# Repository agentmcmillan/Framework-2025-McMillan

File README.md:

# Framework-2025-Badge
Frame:Work NYC 2025 Interactive Pixel Badge Kitty - Badges Generously "sponsored" by Fuse Technical Group https://www.fuse-tg.com

# Getting started with the software.

## Tutorial Resources

Tutorial code for setting up the LED matrix display can be found here:
https://github.com/mkohler99/FrameworkNYBadge_Tutorials/

## Firmware Examples in This Repository

This repository includes several ready-to-use firmware examples:

### 1. LED Ripple Animation

Button-triggered rainbow ripple animation that demonstrates:
- LED matrix addressing and control
- Button input handling
- Safe power management (15% brightness limit)
- HSV to RGB color conversion
- Idle breathing animation

Press the center "MEOW" button to trigger a rainbow ripple effect emanating from the center of the display.

**Available in two versions:**
- **Arduino (Recommended)**: `LED_Ripple_Arduino/LED_Ripple_Arduino.ino` - Runs continuously with idle animation
- **MicroPython**: `led_ripple.py` - Simple script version

### 2. Badge LED + TFT Demo (Arduino)
**Directory:** `Badge_LED_TFT_Demo/`

Combines LED matrix control with a GC9A01 round TFT display (240×240) for enhanced interactivity:
- Rainbow ripple animation on LED matrix (center button triggered)
- Real-time battery voltage monitoring with color-coded display
- Button state indicators
- Simultaneous multi-display control
- Safe power management

**Required Hardware:**
- GC9A01 round TFT display connected via Whisker expansion port

**Documentation:**
- `README.md` - Complete feature overview
- `QUICK_START.md` - 5-minute setup guide
- `WIRING.txt` - Pin connection details

### 3. Dual-MCU WiFi Integration (Arduino)
**Directory:** `Dual_MCU_Integration/`

Advanced system that adds WiFi and Bluetooth capabilities using an ESP32-S3 coprocessor connected via the SAO port:

**Features:**
- **WiFi Access Point** - Connect your phone to "PixelKitty-XXXX" network
- **Web-based LED Designer** - Draw custom patterns on a 15×7 grid in your browser
- **QR Code Display** - Shows WiFi credentials on TFT display (press RIGHT button)
- **Animated Cat** - Pixel art cat walks across TFT after QR timeout
- **BLE Beacon** - Broadcast custom messages via Bluetooth
- **I2C Communication** - RP2040 and ESP32-S3 communicate at 100kHz

**Firmware Versions:**
- **Basic:** `RP2040_Master/` + `ESP32_S3_Slave/` - I2C foundation
- **Enhanced:** `RP2040_Enhanced/` + `ESP32_S3_Enhanced/` - Full features (QR, cat, web)

**Web Interface:**
- `Web_Interface/led_matrix.html` - Interactive LED pattern designer

**Required Hardware:**
- ESP32-S3 development board connected to SAO port (4-pin I2C)

**Comprehensive Documentation:**
- `README.md` - System architecture overview
- `GETTING_STARTED.md` - Quick start guide
- `ENHANCED_FEATURES.md` - QR code and web interface details
- `LIBRARY_SETUP.md` - Required Arduino libraries
- `ESP32_S3_SETUP.md` - Board support installation
- `WIRING.txt` - SAO port connection diagram
- `INDEX.md` - File organization guide
- `FUTURE_FEATURES.md` - Planned expansions

## Graphics Libraries

### Seeed_GFX Library
**Directory:** `Seeed_GFX-master/`

TFT_eSPI-based graphics library with 188+ example sketches for TFT displays:
- Clock displays, animations, sprites
- Touch panel support
- PNG/JPG decoding
- GUI widgets (buttons, meters, sliders)
- E-Paper display support
- DMA acceleration for RP2040

### Seeed Round Display Library
**Directory:** `Seeed_Arduino_RoundDisplay-main/`

LVGL-based UI library for round TFT displays with hardware test sketches and GIF player support.

## Repository Structure

```
Framework-2025-McMillan/
├── HARDWARE/                          # Hardware design files
│   ├── KiCad/TagTag/                 # KiCad project (schematic, PCB, libraries)
│   ├── Gerber/                       # Manufacturing files (ready for PCB fab)
│   └── Documentation/                # PDFs, BOM, 3D models, renders
├── LED_Ripple_Arduino/               # Arduino: Rainbow ripple animation (recommended)
├── Badge_LED_TFT_Demo/               # Arduino: LED matrix + TFT display demo
├── Dual_MCU_Integration/             # Arduino: ESP32-S3 WiFi/BLE expansion
│   ├── RP2040_Master/                # Basic I2C master firmware
│   ├── RP2040_Enhanced/              # Enhanced with QR code + animated cat
│   ├── ESP32_S3_Slave/               # Basic I2C slave with WiFi/BLE
│   ├── ESP32_S3_Enhanced/            # Enhanced with web server + captive portal
│   └── Web_Interface/                # Browser-based LED designer
├── Seeed_GFX-master/                 # TFT graphics library (188+ examples)
├── Seeed_Arduino_RoundDisplay-main/  # LVGL library for round displays
├── led_ripple.py                     # MicroPython LED animation example
└── README.md                         # This file
```

# Getting started with the hardware.

The FrameWork badge was designed with the following features

Easy to use RP2040 platform for hacking
Low Resolution 15x7 Pixel Matrix Display
4MB of on board flash storage
3 Buttons and a dedicated power switch
USB Type C for power and uploading software
2x AA battery holder for power on the go
Infrared Sender and Receiver for interactive experiences
Optional expansion headers for hardware hacking

Getting started with the RP2040
The raspberry pi RP2040 chip is super easy to use. Because this design is based on the Raspberry Pi Pico, a wide variety of tutorials and example code exists for this platform. 

More information about the RP2040 can be found here https://www.raspberrypi.com/documentation/microcontrollers/silicon.html#rp2040

This guide from Adafruit is super helpful for understand how to setup an Arduino style development environment
https://learn.adafruit.com/adafruit-feather-rp2040-pico/arduino-ide-setup

To program the Badge, simply put it in bootloader mode by plugging it into the computer you want to program it with, holding down the 'BOOT' button and then tapping the 'RESET' button. This will cause the RP2040 to start in bootloader mode and enumerate as a USB drive on the host computer. Compiled code can be copied to the device in this state and will run on reboot. Alternatively, various development environments can flash the chip while it's in this state. We recommend starting with Arduino, or if you are more comfortable with C/C++, Visual Studio Code.

# Getting Started With Framework Badge and Arduino

<<ARDUINO EXAMPLE>>

# Framework Badge Pinout

The RP2040 references its pins with an IO number. Your code will use these numbers to refer to the devices you wish to control. For example, if you want to blink the onboard status LED (labelled "Blink!") you would define and output pin on IO#11, as that LED is wired to IO#11.

Your badge has the following IO available:

## LED Matrix Display - IO#4

The LED Matrix is an array of WS2812B-2020 RGB LEDs arranged in a 15 column by 7 row grid. The LED's are addressed from Top Left to Bottom Right in columns going from top to bottom. The first Column is made of LEDs 1-7, the next 8-14, the next 15-21, and so on. The connection of the LEDs **DOES NOT** flow snake-wise, columns are always numbered from top to bottom. 

When using a large number of these LEDs power draw can get out of control. Each LED channel 'Red' 'Green' or 'Blue' can use up to 12mA of current, for a total of 36mA per LED. With 107 LED's you could theoretically draw up to 3,852mA of current, however the board can really only supply around 2500mA of current reliably. For this reason, 

**NEVER POWER THE LED MATRIX AT FULL BRIGHTNESS IN WHITE**

. Many LED software libraries, such as FastLED have the ability to estimate power usage at runtime to set proper maximum levels that vary dynamically with the number of pixels lit and what color they are. In our normal Badge Application, drawing text on the display, we statistically light up less than 1/4 of the pixels at any given moment, and have the brightness set to less than 25%. This gives us at least 8 hours of run time on batteries and keeps the power usage within reasonable limits, plus the LED's are distractingly too bright at full power anyway. **Failure to properly manage the LED matrix's power can result in hardware damage, quickly depleted batteries, and risk of burns from overheated components, so please be careful**

More information about he WS2812B 2020 LEDs used in this project can be found at the data sheet here: 
https://www.lcsc.com/datasheet/C965555.pdf

## Infrared Transmitter - IO#3

The Infrared TX is simply an Infrared LED that you can blink on and off really fast to send data, like a universal remote. (In fact, if you wanted to you could probably program your badge to emulate remote control signals and wreak havoc in a Buffalo Wild Wings, but please use this feature responsibly) This LED emits light in the 940nm range, typical for IR applications. In our laser tag application we're using a 38khz modulation scheme, which is common for remote control applications.

## Buttons - IO#5, 6, and 7

IO Pins can also be configured as inputs to read the state of buttons. The buttons on this badge are normally open and are considered pressed when they are pulled to ground. The buttons are IO#5-7 from Left to Right

## Infrared Receiver - IO#27

The Infrared Receiver used is specifically designed for Remote Control applications and is designed specifically for 38khz modulated signals. This means that there is logic in the receiver itself designed to filter out noise at other frequencies, such as fluorescent lighting. 

More information about the IRM-H638T/TR2 can be found at the data sheet here:
https://www.everlighteurope.com/custom/files/datasheets/DMO-0000008.pdf

## Battery Voltage Monitor - IO#26

The badge has the ability to monitor the voltage of the AA batteries through a voltage divider. The voltage divider scales the voltage by .357 allowing for you to measure the battery voltage in a range of 0-9v (However it should never exceed 3v. 

## Red LED - IO#11

The badge features a simple LED you can blink on and off for testing

## USB Port

The onboard USB port can be configured with various libraries, such as Tiny USB, for all sorts of neat applications, from serial interfaces to keyboard emulators, to audio devices. We've used this chip's USB functionality in the past to emulate a USB sound card to provide timecode to windows computers.

# Expansion Port Pinouts

## Expansion "Whisker" Port

Because our badge is kitty cat shaped, we named our expansion ports 'Whiskers' Many dev boards create their own custom standards for expansion boards, so why cant us.

These ports are usually non soldered on production badges, however simple 1x5 header sockets can be soldered in place to allow for modules to stack onto the bottom side of the board. 

The following IO is available:
- **+5V** - For powering LEDs
- **+3.3V** - For powering other devices
- **GND** - Very important
- **IO#23, 24, and 25** - For connecting to various external devices (SPI/I2C capable)
- **IO#28 (ADC#2)** - A special analog input pin that can read voltages, useful for sensors

### TFT Display Expansion

The Whisker port is ideal for connecting TFT displays via SPI. This repository includes two graphics libraries (`Seeed_GFX-master/` and `Seeed_Arduino_RoundDisplay-main/`) with 188+ example sketches for driving TFT displays.

**Common TFT Pin Mapping (via Whisker Port):**
- **SPI MOSI:** IO#23 or IO#24
- **SPI SCK:** IO#24 or IO#25
- **CS (Chip Select):** Any available GPIO
- **DC (Data/Command):** Any available GPIO
- **RST (Reset):** Any available GPIO (or tie to 3.3V rail)
- **Power:** 3.3V for logic, 5V for backlight (if needed)

See the `Badge_LED_TFT_Demo/` example for a complete implementation using a GC9A01 round display.

The following image shows how these pins are laid out. The schematic and PCB files included in this repository can show how to build a board that connects to this expansion port.

## DVI "Whisker" Port

We chose to add DVI output to our board using an existing open source board called the DVI Sock. This board connects a specific set of IO pins to an HDMI plug in order to allow the RP2040 to drive a display with a 640x480 DVI signal. 

The DVI Sock can be found here:
https://www.adafruit.com/product/5957

More information about the DVI Sock and its implementation can be found at the original creator's GitHub: 
https://github.com/Wren6991/Pico-DVI-Sock
We take no credit for how this feature works, we are simply passing the needed IO through our board from the RP2040 to the pins for the expansion board to make it easier to experiment with this functionality. 

The DVI expansion uses IO#12-IO#19

## SAO Port

In the badge hacking community, a standard developed for connecting Simple Add Ons to existing hardware badges, using a 4-6 pin socket on the badge with matching pins on the add on. This allows for hackers to dress their badges up with flair that pulls power from the main badge. We are able to re-use some of the whisker header pins in a slightly different shape to allow for a basic 4 pin SAO port, when a header is soldered to the top side of the badge. 

More information about the SAO standard can be found on the creator's page here:
https://hackaday.io/project/52950-shitty-add-ons/log/159806-introducing-the-shitty-add-on-v169bis-standard
We only implement the v0.1 version of this standard with 4 pins, however a full 6 pin SAO will fit mechanically without conflict

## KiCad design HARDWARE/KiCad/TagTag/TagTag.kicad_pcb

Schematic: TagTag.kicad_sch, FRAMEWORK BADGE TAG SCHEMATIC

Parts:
BT1, BT2: BH-AA-A5BJ012; BAT_BH-AA-A5BJ012; PARTREV D; LCSC C5290180
C1, C2, C5, C6, C7, C8, C10, C11, C13, C16: 100nF; C_0603_1608Metric; LCSC C5137636
C3, C4, C20, C27, C28: 1uF; C_0603_1608Metric; LCSC C5137472
C9, C12: 10uF; C_0603_1608Metric; LCSC C5137497
C14, C15: 22pF; C_0603_1608Metric; LCSC C7419421
C23, C30: 10uF; C_0805_2012Metric; LCSC C1713
C24, C25, C26: 47uF; C_0805_2012Metric; LCSC C16780
C29: 22uF; C_0805_2012Metric; LCSC C5137600
D1, D2, D3: LED 0805 RED; LED_0805_2012Metric; LCSC C965812
D5: IR15-21C/TR8; LED_1206_3216Metric; LCSC C22357565
D301, D302, D303, D304, D305, D306, D307, D308, D309, D310, D311, D312, D313, D314, D315, D316, D317, D318, D319, D320, D321, D322, D323, D324, D325, D326, D327, D328, D329, D330, D331, D332, D333, D334, D335, D336, D337, D338, D339, D340, D341, D342, D343, D344, D345, D346, D347, D348, D349, D350, D351, D352, D353, D354, D355, D356, D357, D358, D359, D360, D361, D362, D363, D364, D365, D366, D367, D368, D369, D370, D371, D372, D373, D374, D375, D376, D377, D378, D379, D380, D381, D382, D383, D384, D385, D386, D387, D388, D389, D390, D391, D392, D393, D394, D395, D396, D397, D398, D399, D400, D401, D402, D403, D404, D405: WS2812B-2020; LED_WS2812B-2020_PLCC4_2.0x2.0mm; LCSC C965555
EAR1, EAR2: Fiducial; Fiducial_1mm_Mask2mm; Manufacturer_Part_Number DNP; LCSC DNP
FID3: Fiducial; Fiducial_1mm_Mask2mm; Manufacturer_Part_Number DNP; LCSC DNP
H7, H8: MountingHole_Pad; MountingHole_2.7mm_M2.5_DIN965_Pad; LCSC DNP
IC1: IRM-H638T_TR2; IRMH638TTR2; Mouser Part Number 638-IRMH638TTR2
J1: GT-USB-7010ASV; USB_C_Receptacle_G-Switch_GT-USB-7010ASV; PARTREV A0; LCSC C2988369
J2: Conn_01x02_Pin; PinHeader_1x02_P2.54mm_Vertical; LCSC DNP
L1: TMPA 0603S-1R0MN-D; LCSC C305186
Q1: AO3406; Manufacturer_Part_Number AO3406; LCSC C2909910
R1, R4: 27.4; R_0603_1608Metric; LCSC C185346
R2: 180K; R_0603_1608Metric; LCSC C123419
R3: 100K; R_0603_1608Metric; LCSC C14675
R5, R6: 5.1K; R_0603_1608Metric; LCSC C105580
R7: 270; R_0603_1608Metric; LCSC C22966
R8: 750; R_0603_1608Metric; LCSC C23241
R10, R13, R16, R27: 10K; R_0603_1608Metric; LCSC C98220
R17: 732K; R_0603_1608Metric; LCSC C246003
R18: 91K; R_0603_1608Metric; LCSC C137671
R21: 120; R_0603_1608Metric; LCSC C177328
R26, R28: 1K; R_0603_1608Metric; LCSC C22548
R29: 150; R_0603_1608Metric; LCSC C114608
SW1, SW3, SW4: GT-TC149A-H060-L1; GT-TC149X; LCSC C2834980
SW2, SW5: PTS526SK08SMTR2LFS; PTS526_0P8_CNK; LCSC C2800848
SW8: MK-12C02-G025; MK-12C02; LCSC C778186
TP1: TestPoint; TestPoint_Pad_1.0x1.0mm; LCSC DNP
U2: RP2040; QFN-56-1EP_7x7mm_P0.4mm_EP3.2x3.2mm; LCSC C2040
U3: SN74LV1T34; SOT-23-5; Manufacturer_Part_Number SN74LV1T34; LCSC C100024
U4: TPS61022RWUR; CONV_TPS61022RWUR; PARTREV 4223724/C 02/2018; LCSC C915088
U5: LM66200DRLR; SOT-5X3_DRL_TEX; LCSC C3235556
U6: AMS1117-3.3; SOT229P700X180-4N; PARTREV NA; LCSC C347222
U7: W25Q32JVSSIQ; SOIC-8_5.23x5.23mm_P1.27mm; LCSC C179173
WIS1, WIS2, WIS3, WIS4: Conn_01x05_Pin; PinSocket_1x05_P2.54mm_Vertical; LCSC DNP
Y1: ABLS-12.000MHZ-B4-T; XTAL_ABLS-12.000MHZ-B4-T; PARTREV 02.16.2021; LCSC C596818

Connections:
+1V1: C1.1, C2.1, C3.1, U2.23 (DVDD), U2.45 (VREG_VOUT), U2.50 (DVDD)
+5V: C30.1, D301.4 (VDD), D302.4 (VDD), D303.4 (VDD), D304.4 (VDD), D305.4 (VDD), D306.4 (VDD), D307.4 (VDD), D308.4 (VDD), D309.4 (VDD), D310.4 (VDD), D311.4 (VDD), D312.4 (VDD), D313.4 (VDD), D314.4 (VDD), D315.4 (VDD), D316.4 (VDD), D317.4 (VDD), D318.4 (VDD), D319.4 (VDD), D320.4 (VDD), D321.4 (VDD), D322.4 (VDD), D323.4 (VDD), D324.4 (VDD), D325.4 (VDD), D326.4 (VDD), D327.4 (VDD), D328.4 (VDD), D329.4 (VDD), D330.4 (VDD), D331.4 (VDD), D332.4 (VDD), D333.4 (VDD), D334.4 (VDD), D335.4 (VDD), D336.4 (VDD), D337.4 (VDD), D338.4 (VDD), D339.4 (VDD), D340.4 (VDD), D341.4 (VDD), D342.4 (VDD), D343.4 (VDD), D344.4 (VDD), D345.4 (VDD), D346.4 (VDD), D347.4 (VDD), D348.4 (VDD), D349.4 (VDD), D350.4 (VDD), D351.4 (VDD), D352.4 (VDD), D353.4 (VDD), D354.4 (VDD), D355.4 (VDD), D356.4 (VDD), D357.4 (VDD), D358.4 (VDD), D359.4 (VDD), D360.4 (VDD), D361.4 (VDD), D362.4 (VDD), D363.4 (VDD), D364.4 (VDD), D365.4 (VDD), D366.4 (VDD), D367.4 (VDD), D368.4 (VDD), D369.4 (VDD), D370.4 (VDD), D371.4 (VDD), D372.4 (VDD), D373.4 (VDD), D374.4 (VDD), D375.4 (VDD), D376.4 (VDD), D377.4 (VDD), D378.4 (VDD), D379.4 (VDD), D380.4 (VDD), D381.4 (VDD), D382.4 (VDD), D383.4 (VDD), D384.4 (VDD), D385.4 (VDD), D386.4 (VDD), D387.4 (VDD), D388.4 (VDD), D389.4 (VDD), D390.4 (VDD), D391.4 (VDD), D392.4 (VDD), D393.4 (VDD), D394.4 (VDD), D395.4 (VDD), D396.4 (VDD), D397.4 (VDD), D398.4 (VDD), D399.4 (VDD), D400.4 (VDD), D401.4 (VDD), D402.4 (VDD), D403.4 (VDD), D404.4 (VDD), D405.4 (VDD), R16.1, R21.1, U3.5 (VCC), U5.2 (VOUT), U5.7 (VOUT), U6.3 (VIN), WIS3.5
+BATT: C23.1, L1.1, R2.1, SW8.3 (C), U4.5 (EN), U4.7 (VIN)
/5V_PXL: D301.3 (DIN), U3.4 (Y)
/AN_ADC2: U2.40 (GPIO28_ADC2), WIS4.1
/AN_BATT_MEASURE_PI: R2.2, R3.1, U2.38 (GPIO26_ADC0)
/DI_23: U2.35 (GPIO23), WIS4.5
/DI_24: J2.2, U2.36 (GPIO24), WIS4.4
/DI_25: U2.37 (GPIO25), WIS3.3, WIS4.2
/DI_BTN_FIRE_PI: SW4.1, SW4.2, U2.9 (GPIO7)
/DI_BTN_L_PI: SW1.1, SW1.2, U2.7 (GPIO5)
/DI_BTN_R_PI: SW3.1, SW3.2, U2.8 (GPIO6)
/DI_IRM_PI: IC1.3 (OUT), U2.39 (GPIO27_ADC1)
/DO_IR_LED_PI: Q1.1 (G), R10.1, U2.5 (GPIO3)
/DVI_12: U2.15 (GPIO12), WIS2.1
/DVI_13: U2.16 (GPIO13), WIS2.2
/DVI_14: U2.17 (GPIO14), WIS2.4
/DVI_15: U2.18 (GPIO15), WIS2.5
/DVI_16: U2.27 (GPIO16), WIS1.5
/DVI_17: U2.28 (GPIO17), WIS1.4
/DVI_18: U2.29 (GPIO18), WIS1.2
/DVI_19: U2.30 (GPIO19), WIS1.1
/GPIO_PXL_PI: U2.6 (GPIO4), U3.2 (A)
/PI_A_3v3: C4.1, C5.1, C6.1, C7.1, C8.1, C9.1, C10.1, C11.1, C13.1, C16.1, C20.1, C29.1, D2.2 (A), IC1.4 (VCC), R13.2, R27.2, U2.1 (IOVDD), U2.10 (IOVDD), U2.22 (IOVDD), U2.33 (IOVDD), U2.42 (IOVDD), U2.43 (ADC_AVDD), U2.44 (VREG_IN), U2.48 (USB_VDD), U2.49 (IOVDD), U6.2 (VOUT), U6.4 (VOUT_(TAB)), U7.8 (VCC), WIS3.1, WIS3.2
/PI_A_LED: D3.2 (A), U2.14 (GPIO11)
/PI_A_USB_C_Data_1_N: R4.2, U2.46 (USB_DM)
/PI_A_USB_C_Data_1_P: R1.2, U2.47 (USB_DP)
/PI_A_USB_C_Data_N: J1.A7 (D1-), J1.B7 (D2-), R4.1
/PI_A_USB_C_Data_P: J1.A6 (D1+), J1.B6 (D2+), R1.1
/PI_A_USB_PWR_IN: C12.1, C28.1, D1.2 (A), J1.A4_B9 (VBUS_A), J1.B4_A9 (VBUS_B), U5.6 (VIN2)
/PI_BOOT: R26.1, SW5.1, SW5.2, TP1.1
/PI_RESET: R13.1, SW2.1, SW2.2, U2.26 (RUN)
/QSPI_SCLK_A: U2.52 (QSPI_SCLK), U7.6 (CLK)
/QSPI_SD0_A: U2.53 (QSPI_SD0), U7.5 (DI(IO0))
/QSPI_SD1_A: U2.55 (QSPI_SD1), U7.2 (DO(IO1))
/QSPI_SD2_A: U2.54 (QSPI_SD2), U7.3 (IO2)
/QSPI_SD3_A: U2.51 (QSPI_SD3), U7.7 (IO3)
/QSPI_SS: R26.2, R27.1, U2.56 (QSPI_SS), U7.1 (~CS)
/XIN_A: C15.1, U2.20 (XIN), Y1.1
/XOUT_A: R28.2, U2.21 (XOUT)
GND: BT2.-, C1.2, C2.2, C3.2, C4.2, C5.2, C6.2, C7.2, C8.2, C9.2, C10.2, C11.2, C12.2, C13.2, C14.2, C15.2, C16.2, C20.2, C23.2, C24.2, C25.2, C26.2, C27.2, C28.2, C29.2, C30.2, D301.2 (VSS), D302.2 (VSS), D303.2 (VSS), D304.2 (VSS), D305.2 (VSS), D306.2 (VSS), D307.2 (VSS), D308.2 (VSS), D309.2 (VSS), D310.2 (VSS), D311.2 (VSS), D312.2 (VSS), D313.2 (VSS), D314.2 (VSS), D315.2 (VSS), D316.2 (VSS), D317.2 (VSS), D318.2 (VSS), D319.2 (VSS), D320.2 (VSS), D321.2 (VSS), D322.2 (VSS), D323.2 (VSS), D324.2 (VSS), D325.2 (VSS), D326.2 (VSS), D327.2 (VSS), D328.2 (VSS), D329.2 (VSS), D330.2 (VSS), D331.2 (VSS), D332.2 (VSS), D333.2 (VSS), D334.2 (VSS), D335.2 (VSS), D336.2 (VSS), D337.2 (VSS), D338.2 (VSS), D339.2 (VSS), D340.2 (VSS), D341.2 (VSS), D342.2 (VSS), D343.2 (VSS), D344.2 (VSS), D345.2 (VSS), D346.2 (VSS), D347.2 (VSS), D348.2 (VSS), D349.2 (VSS), D350.2 (VSS), D351.2 (VSS), D352.2 (VSS), D353.2 (VSS), D354.2 (VSS), D355.2 (VSS), D356.2 (VSS), D357.2 (VSS), D358.2 (VSS), D359.2 (VSS), D360.2 (VSS), D361.2 (VSS), D362.2 (VSS), D363.2 (VSS), D364.2 (VSS), D365.2 (VSS), D366.2 (VSS), D367.2 (VSS), D368.2 (VSS), D369.2 (VSS), D370.2 (VSS), D371.2 (VSS), D372.2 (VSS), D373.2 (VSS), D374.2 (VSS), D375.2 (VSS), D376.2 (VSS), D377.2 (VSS), D378.2 (VSS), D379.2 (VSS), D380.2 (VSS), D381.2 (VSS), D382.2 (VSS), D383.2 (VSS), D384.2 (VSS), D385.2 (VSS), D386.2 (VSS), D387.2 (VSS), D388.2 (VSS), D389.2 (VSS), D390.2 (VSS), D391.2 (VSS), D392.2 (VSS), D393.2 (VSS), D394.2 (VSS), D395.2 (VSS), D396.2 (VSS), D397.2 (VSS), D398.2 (VSS), D399.2 (VSS), D400.2 (VSS), D401.2 (VSS), D402.2 (VSS), D403.2 (VSS), D404.2 (VSS), D405.2 (VSS), H7.1, H8.1, IC1.1 (GND_1), IC1.2 (GND_2), J1.A1_B12 (GND_A), J1.B1_A12 (GND_B), J1.SH1 (SHIELD), J1.SH2 (SHIELD), J1.SH3 (SHIELD), J1.SH4 (SHIELD), J2.1, Q1.2 (S), R3.2, R5.2, R6.2, R7.1, R8.1, R10.2, R18.2, R29.1, SW1.3, SW1.4, SW2.3, SW2.4, SW3.3, SW3.4, SW4.3, SW4.4, SW5.3, SW5.4, U2.19 (TESTEN), U2.57 (GND), U3.3 (GND), U4.1 (GND), U4.6 (MODE), U5.1 (GND), U5.4 (ON), U5.5 (GND), U6.1 (ADJ/GND), U7.4 (GND), WIS1.3, WIS2.3, WIS4.3
unnamed: BT1.-, BT2.+
unnamed: C14.1, R28.1, Y1.2
unnamed: D1.1 (K), R7.2
unnamed: D2.1 (K), R8.2
unnamed: D3.1 (K), R29.2
unnamed: D5.2 (A), R21.2
unnamed: D5.1 (K), Q1.3 (D)
unnamed: D301.1 (DOUT), D302.3 (DIN)
unnamed: D302.1 (DOUT), D303.3 (DIN)
unnamed: D303.1 (DOUT), D304.3 (DIN)
unnamed: D304.1 (DOUT), D305.3 (DIN)
unnamed: D305.1 (DOUT), D306.3 (DIN)
unnamed: D306.1 (DOUT), D307.3 (DIN)
unnamed: D307.1 (DOUT), D308.3 (DIN)
unnamed: D308.1 (DOUT), D309.3 (DIN)
unnamed: D309.1 (DOUT), D310.3 (DIN)
unnamed: D310.1 (DOUT), D311.3 (DIN)
unnamed: D311.1 (DOUT), D312.3 (DIN)
unnamed: D312.1 (DOUT), D313.3 (DIN)
unnamed: D313.1 (DOUT), D314.3 (DIN)
unnamed: D314.1 (DOUT), D315.3 (DIN)
unnamed: D315.1 (DOUT), D316.3 (DIN)
unnamed: D316.1 (DOUT), D317.3 (DIN)
unnamed: D317.1 (DOUT), D318.3 (DIN)
unnamed: D318.1 (DOUT), D319.3 (DIN)
unnamed: D319.1 (DOUT), D320.3 (DIN)
unnamed: D320.1 (DOUT), D321.3 (DIN)
unnamed: D321.1 (DOUT), D322.3 (DIN)
unnamed: D322.1 (DOUT), D323.3 (DIN)
unnamed: D323.1 (DOUT), D324.3 (DIN)
unnamed: D324.1 (DOUT), D325.3 (DIN)
unnamed: D325.1 (DOUT), D326.3 (DIN)
unnamed: D326.1 (DOUT), D327.3 (DIN)
unnamed: D327.1 (DOUT), D328.3 (DIN)
unnamed: D328.1 (DOUT), D329.3 (DIN)
unnamed: D329.1 (DOUT), D330.3 (DIN)
unnamed: D330.1 (DOUT), D331.3 (DIN)
unnamed: D331.1 (DOUT), D332.3 (DIN)
unnamed: D332.1 (DOUT), D333.3 (DIN)
unnamed: D333.1 (DOUT), D334.3 (DIN)
unnamed: D334.1 (DOUT), D335.3 (DIN)
unnamed: D335.1 (DOUT), D336.3 (DIN)
unnamed: D336.1 (DOUT), D337.3 (DIN)
unnamed: D337.1 (DOUT), D338.3 (DIN)
unnamed: D338.1 (DOUT), D339.3 (DIN)
unnamed: D339.1 (DOUT), D340.3 (DIN)
unnamed: D340.1 (DOUT), D341.3 (DIN)
unnamed: D341.1 (DOUT), D342.3 (DIN)
unnamed: D342.1 (DOUT), D343.3 (DIN)
unnamed: D343.1 (DOUT), D344.3 (DIN)
unnamed: D344.1 (DOUT), D345.3 (DIN)
unnamed: D345.1 (DOUT), D346.3 (DIN)
unnamed: D346.1 (DOUT), D347.3 (DIN)
unnamed: D347.1 (DOUT), D348.3 (DIN)
unnamed: D348.1 (DOUT), D349.3 (DIN)
unnamed: D349.1 (DOUT), D350.3 (DIN)
unnamed: D350.1 (DOUT), D351.3 (DIN)
unnamed: D351.1 (DOUT), D352.3 (DIN)
unnamed: D352.1 (DOUT), D353.3 (DIN)
unnamed: D353.1 (DOUT), D354.3 (DIN)
unnamed: D354.1 (DOUT), D355.3 (DIN)
unnamed: D355.1 (DOUT), D356.3 (DIN)
unnamed: D356.1 (DOUT), D357.3 (DIN)
unnamed: D357.1 (DOUT), D358.3 (DIN)
unnamed: D358.1 (DOUT), D359.3 (DIN)
unnamed: D359.1 (DOUT), D360.3 (DIN)
unnamed: D360.1 (DOUT), D361.3 (DIN)
unnamed: D361.1 (DOUT), D362.3 (DIN)
unnamed: D362.1 (DOUT), D363.3 (DIN)
unnamed: D363.1 (DOUT), D364.3 (DIN)
unnamed: D364.1 (DOUT), D365.3 (DIN)
unnamed: D365.1 (DOUT), D366.3 (DIN)
unnamed: D366.1 (DOUT), D367.3 (DIN)
unnamed: D367.1 (DOUT), D368.3 (DIN)
unnamed: D368.1 (DOUT), D369.3 (DIN)
unnamed: D369.1 (DOUT), D370.3 (DIN)
unnamed: D370.1 (DOUT), D371.3 (DIN)
unnamed: D371.1 (DOUT), D372.3 (DIN)
unnamed: D372.1 (DOUT), D373.3 (DIN)
unnamed: D373.1 (DOUT), D374.3 (DIN)
unnamed: D374.1 (DOUT), D375.3 (DIN)
unnamed: D375.1 (DOUT), D376.3 (DIN)
unnamed: D376.1 (DOUT), D377.3 (DIN)
unnamed: D377.1 (DOUT), D378.3 (DIN)
unnamed: D378.1 (DOUT), D379.3 (DIN)
unnamed: D379.1 (DOUT), D380.3 (DIN)
unnamed: D380.1 (DOUT), D381.3 (DIN)
unnamed: D381.1 (DOUT), D382.3 (DIN)
unnamed: D382.1 (DOUT), D383.3 (DIN)
unnamed: D383.1 (DOUT), D384.3 (DIN)
unnamed: D384.1 (DOUT), D385.3 (DIN)
unnamed: D385.1 (DOUT), D386.3 (DIN)
unnamed: D386.1 (DOUT), D387.3 (DIN)
unnamed: D387.1 (DOUT), D388.3 (DIN)
unnamed: D388.1 (DOUT), D389.3 (DIN)
unnamed: D389.1 (DOUT), D390.3 (DIN)
unnamed: D390.1 (DOUT), D391.3 (DIN)
unnamed: D391.1 (DOUT), D392.3 (DIN)
unnamed: D392.1 (DOUT), D393.3 (DIN)
unnamed: D393.1 (DOUT), D394.3 (DIN)
unnamed: D394.1 (DOUT), D395.3 (DIN)
unnamed: D395.1 (DOUT), D396.3 (DIN)
unnamed: D396.1 (DOUT), D397.3 (DIN)
unnamed: D397.1 (DOUT), D398.3 (DIN)
unnamed: D398.1 (DOUT), D399.3 (DIN)
unnamed: D399.1 (DOUT), D400.3 (DIN)
unnamed: D400.1 (DOUT), D401.3 (DIN)
unnamed: D401.1 (DOUT), D402.3 (DIN)
unnamed: D402.1 (DOUT), D403.3 (DIN)
unnamed: D403.1 (DOUT), D404.3 (DIN)
unnamed: D404.1 (DOUT), D405.3 (DIN)
unnamed: J1.A5 (CC1), R5.1
unnamed: J1.B5 (CC2), R6.1
unnamed: BT1.+, SW8.2 (B)
unnamed: R17.2, R18.1, U4.4 (FB)
unnamed: L1.2, U4.2 (SW)
unnamed: C24.1, C25.1, C26.1, C27.1, R17.1, U4.3 (VOUT), U5.3 (VIN1)
unnamed: R16.2, U5.8 (ST)

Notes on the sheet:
RIGHT BUTTON IO#6
RP2040 MCU BASED ON RASPBERRY PI RP2040 MINIMAL DESIGN EXAMPLE https://datasheets.raspberrypi.com/rp2040/Minimal-KiCAD.zip
LED PIXEL ARRAY IO#4 - 15 Columns of 7
940NM LED 31mA
C513 by pin 44
EXPANSION HEADERS
BUTTONS
BOOT BUTTON
IDEAL DIODE SWITCHOVER - SELECT USB OR BATTERY POWER
PDN
LEVEL SHIFT FOR PIXEL DATA
INFRARED TRANSMITTER IO#3
RESET BUTTON
POWER SUPPLY
INFRARED RECEIVER - 38KHZ MODULATION BASED ON IRM-H638T/TR2 APPLICATION CIRCUIT IO#27
"MEOW" BUTTON IO#7
SAO BODGE ALLOWS SAO ADDONS TO MATE WITH WHISKER HEADER PIN 2 AND 3 (See Figure 1)
USB TYPE C CONNECTOR
Based on AMS1117 Typical Application Circuit 5V Input, 1 Amp @ 3.3V Output
RED LED IO#11
WIS3 PIN 3 IO#25
4MB SPI Flash
LEFT BUTTON IO#5
FIGURE 1, SAO PORT LAYOUT (PINOUT VIEWED FROM TOP)
BATTERY VOLTAGE SENSOR IO#26
INFRARED TRANSCIEVER
RP2040 - MAIN CPU
3.3V POWER SUPPLY - POWER FOR MCU AND LOGIC
Based on Texas Instruments WEBENCH design 2-3V Input, 2.5 Amp @ 5V Output, Efficiency: 88%
MECHANICAL / FABRICATION
J2 PIN 1 GND
Crystal
CC Resistors configured for 3A @ 5V
Based on Texas Instruments LM66200DLR Reference Design 5V Input, 2.5 Amp @ 5V Output
J2 PIN 2 IO#24
BATTERY SUPPLY AND POWER SWITCH
POWER STATUS LEDS
EXPANSION WHISKER MATES WITH CUSTOM EXPANSION WHISKER BOARDS
SPARKLING DVI HEADER MATES WITH ADAFRUIT DVI SOCK PART 5957 https://www.adafruit.com/product/5957
2.5A

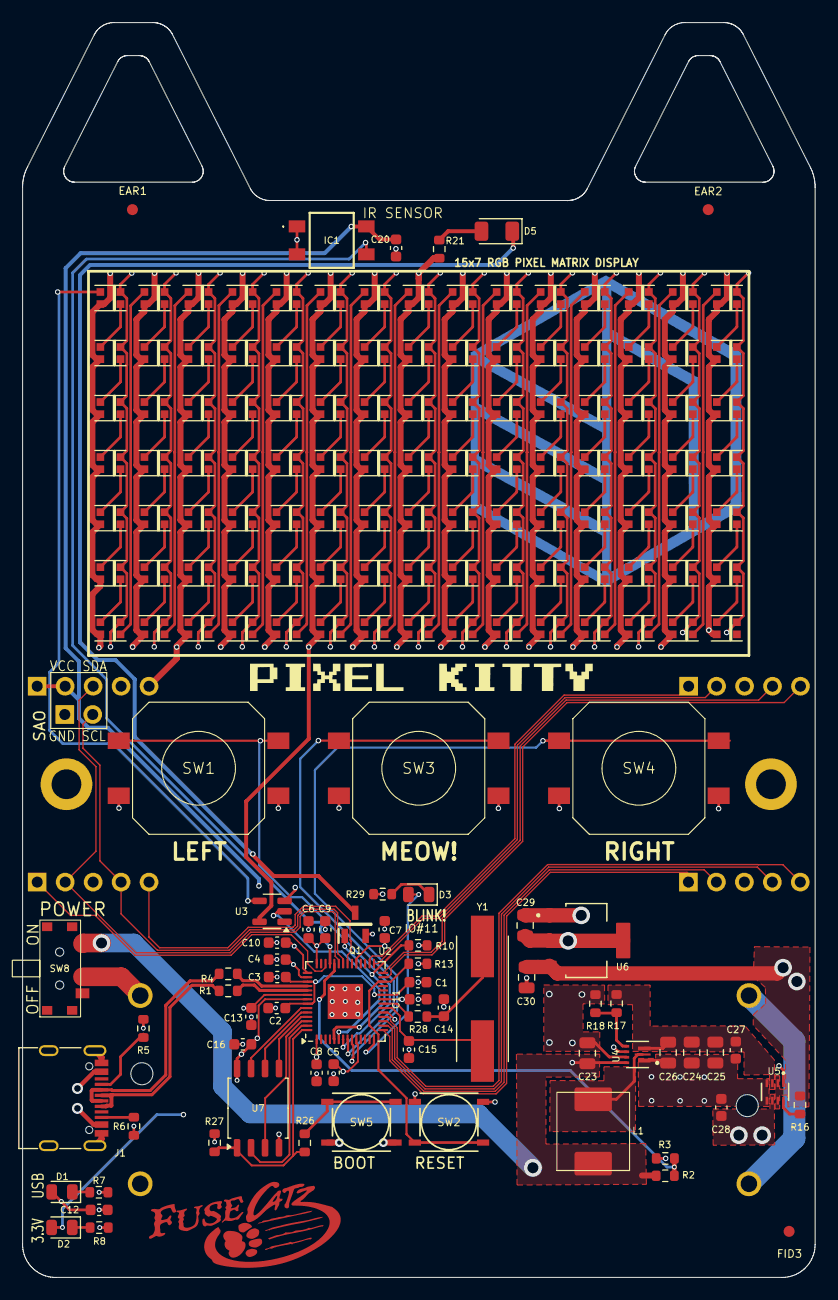
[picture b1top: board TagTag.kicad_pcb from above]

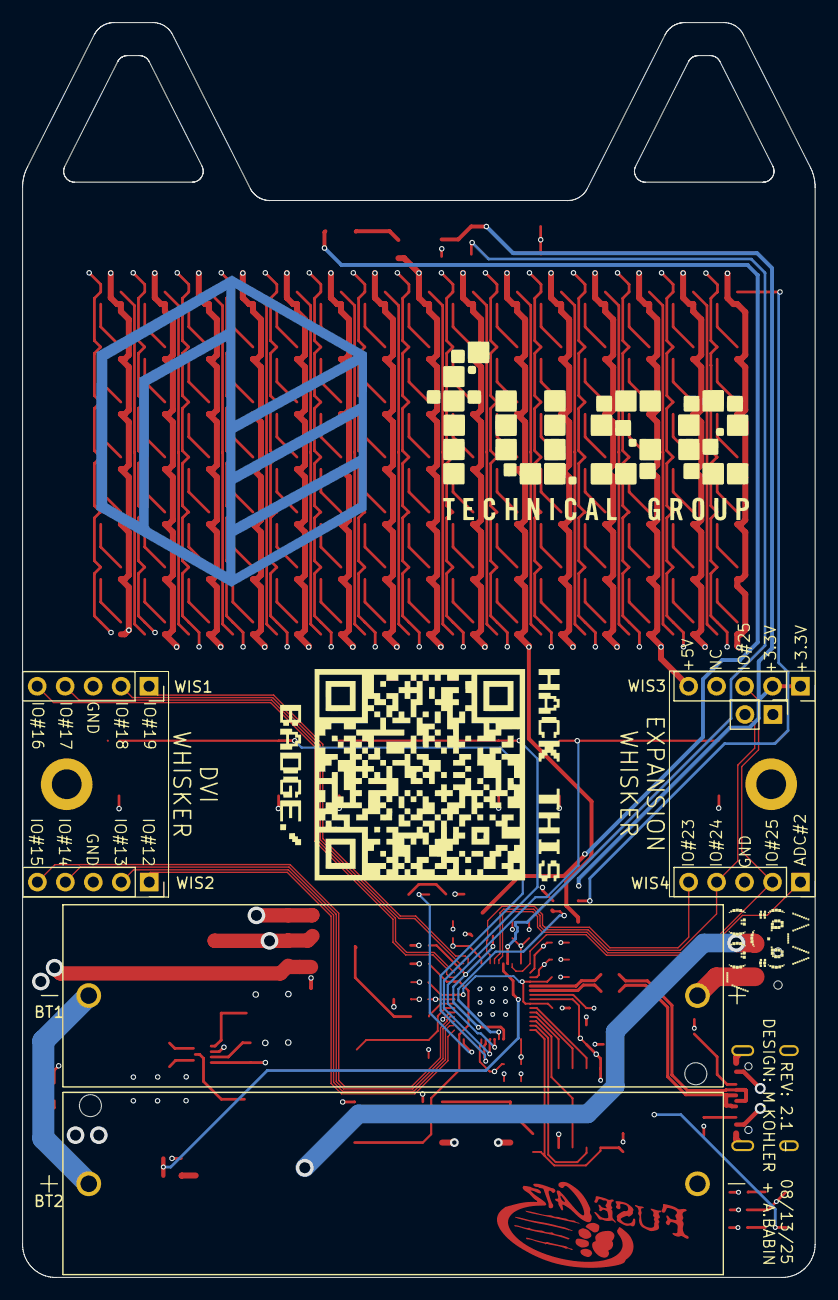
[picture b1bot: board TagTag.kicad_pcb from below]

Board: 4 copper layers, 72.0 x 114.0 mm, 181 parts (7 on the bottom side), 159 nets.

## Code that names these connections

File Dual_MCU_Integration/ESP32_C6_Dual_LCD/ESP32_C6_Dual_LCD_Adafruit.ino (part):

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 * Pin Assignments:
 * Display 1 (Left Eye):
 *   - CS:   GPIO2 (D0)
 *   - DC:   GPIO3 (D1)
 *   - RST:  GPIO4 (D2)
 *   - MOSI: GPIO21 (shared SPI)
 *   - SCK:  GPIO20 (shared SPI)
 *
 * Display 2 (Right Eye):
 *   - CS:   GPIO5 (D3)
 *   - DC:   GPIO6 (D4)
 *   - RST:  GPIO7 (D5)
 *   - MOSI: GPIO21 (shared SPI, same as Display 1)
 *   - SCK:  GPIO20 (shared SPI, same as Display 1)
 *
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
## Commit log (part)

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2025-08-16 Update LICENSE
2025-08-16 Add Hardware Documentation
2025-08-16 Add Software Folder to structure
2025-08-17 Update README.md
    Formatted Images
2025-08-19 Update README.md
    add scare quotes around sponsored
2025-08-22 Repair broken git submodule
2025-09-21 Update README.md to include link to software tutorials
2025-10-19 initl
2025-10-20 Version 1 of IR working
2025-10-21 Inital upload
2025-10-21 Update README.md
    readme update
2025-10-21 convert led ripple to arduino
2025-10-21 more cat
2025-10-28 It works, i think
2025-10-30 dual screen
2025-10-30 updated for c6 gfx support
2025-10-31 change over to pro s3
2025-11-03 More thigns
2025-11-04 More changes
2025-11-04 updated charms
2025-11-04 text modes
2025-11-04 added cheatcodes
2025-11-04 more cheat codes
2025-11-04 now with more sleep
2025-11-04 Adds ice Effect, a simple palette swap of fire, and implements a variable to track number of effects for looping them when the button is pressed
2025-11-04 Adds Matrix Pixel Rain FX
2025-11-04 Adds Firework Effect, Refines colors of Ice effect
2025-11-04 Sooner or later, everyone needs chevrons, recognizing this fact of like, MK includes a chevron module for all your chevron needs
2025-11-04 rip off bugs module from d3
2025-11-05 added sleep bits
2025-11-05 Toy Mode
2025-11-05 score backend code
2025-11-05 logos
2025-11-05 score UART code working
2025-11-05 colorbars
2025-11-05 batteries not included
2025-11-05 fixed battery
2025-11-06 First production build
